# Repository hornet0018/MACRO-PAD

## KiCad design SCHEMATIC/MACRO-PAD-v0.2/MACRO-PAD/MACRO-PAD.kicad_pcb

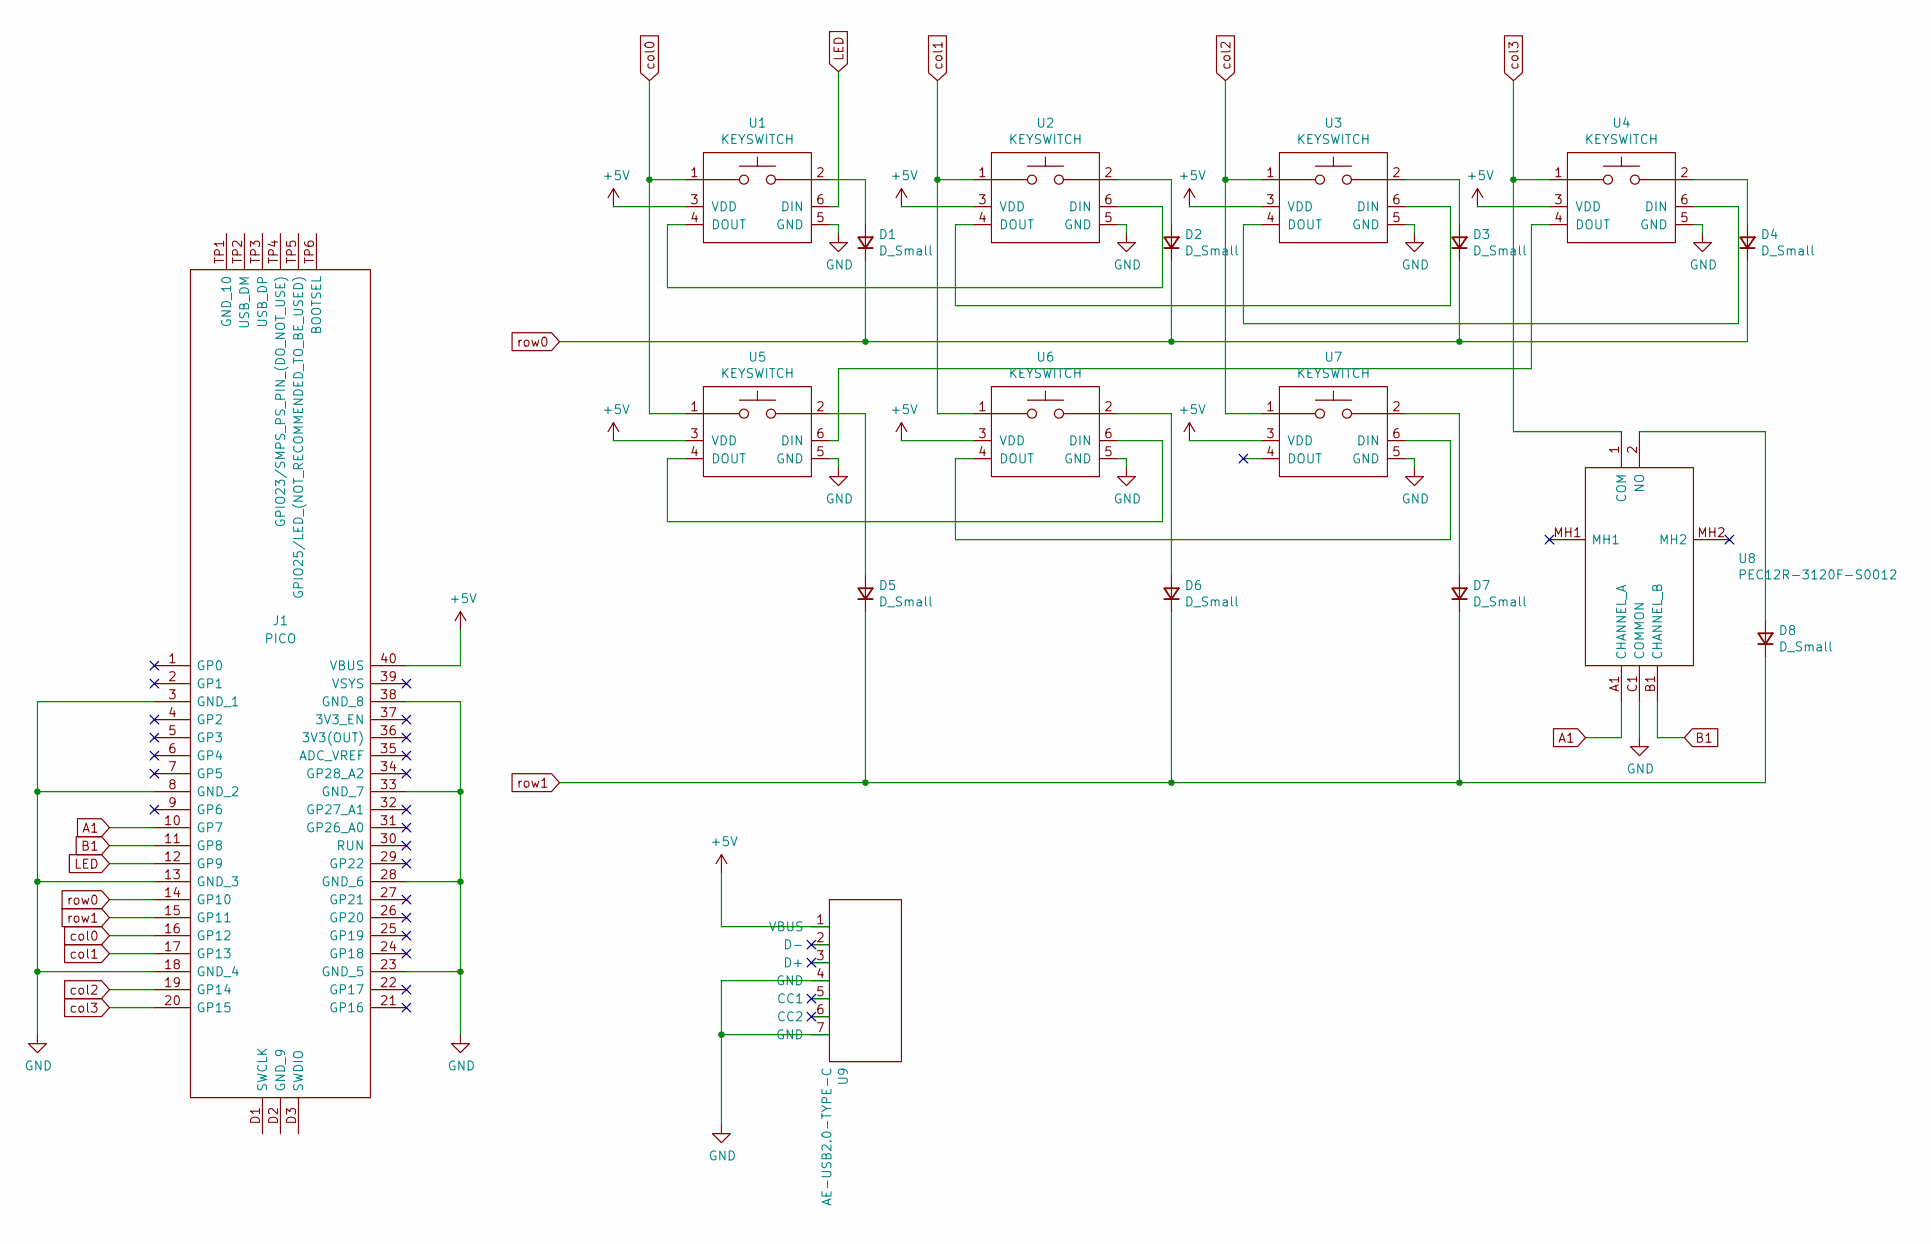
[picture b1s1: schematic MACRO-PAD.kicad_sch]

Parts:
D1, D2, D3, D4, D5, D6, D7, D8: D_Small; D_SOD-123
J1: PICO; RPi_Pico_SMD_TH; Manufacturer_Part_Number PICO
U1, U2, U3, U4, U5, U6, U7: KEYSWITCH; Kailh_socket_MX
U8: PEC12R-3120F-S0012; PEC12R3120FS0012; Manufacturer_Part_Number PEC12R-3120F-S0012; Mouser Part Number 652-PEC12R3120FS0012
U9: AE-USB2.0-TYPE-C

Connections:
+5V: J1.40 (VBUS), U1.3 (VDD), U2.3 (VDD), U3.3 (VDD), U4.3 (VDD), U5.3 (VDD), U6.3 (VDD), U7.3 (VDD), U9.1 (VBUS)
A1: J1.10 (GP7), U8.A1 (CHANNEL_A)
B1: J1.11 (GP8), U8.B1 (CHANNEL_B)
GND: J1.3 (GND_1), J1.8 (GND_2), J1.13 (GND_3), J1.18 (GND_4), J1.23 (GND_5), J1.28 (GND_6), J1.33 (GND_7), J1.38 (GND_8), U1.5 (GND), U2.5 (GND), U3.5 (GND), U4.5 (GND), U5.5 (GND), U6.5 (GND), U7.5 (GND), U8.C1 (COMMON), U9.4 (GND), U9.7 (GND)
LED: J1.12 (GP9), U1.6 (DIN)
unnamed: D1.2 (A), U1.2
unnamed: D2.2 (A), U2.2
unnamed: D3.2 (A), U3.2
unnamed: D4.2 (A), U4.2
unnamed: D5.2 (A), U5.2
unnamed: D6.2 (A), U6.2
unnamed: D7.2 (A), U7.2
unnamed: D8.2 (A), U8.2 (NO)
unnamed: U1.4 (DOUT), U2.6 (DIN)
unnamed: U2.4 (DOUT), U3.6 (DIN)
unnamed: U3.4 (DOUT), U4.6 (DIN)
unnamed: U4.4 (DOUT), U5.6 (DIN)
unnamed: U5.4 (DOUT), U6.6 (DIN)
unnamed: U6.4 (DOUT), U7.6 (DIN)
col0: J1.16 (GP12), U1.1, U5.1
col1: J1.17 (GP13), U2.1, U6.1
col2: J1.19 (GP14), U3.1, U7.1
col3: J1.20 (GP15), U4.1, U8.1 (COM)
row0: D1.1 (K), D2.1 (K), D3.1 (K), D4.1 (K), J1.14 (GP10)
row1: D5.1 (K), D6.1 (K), D7.1 (K), D8.1 (K), J1.15 (GP11)

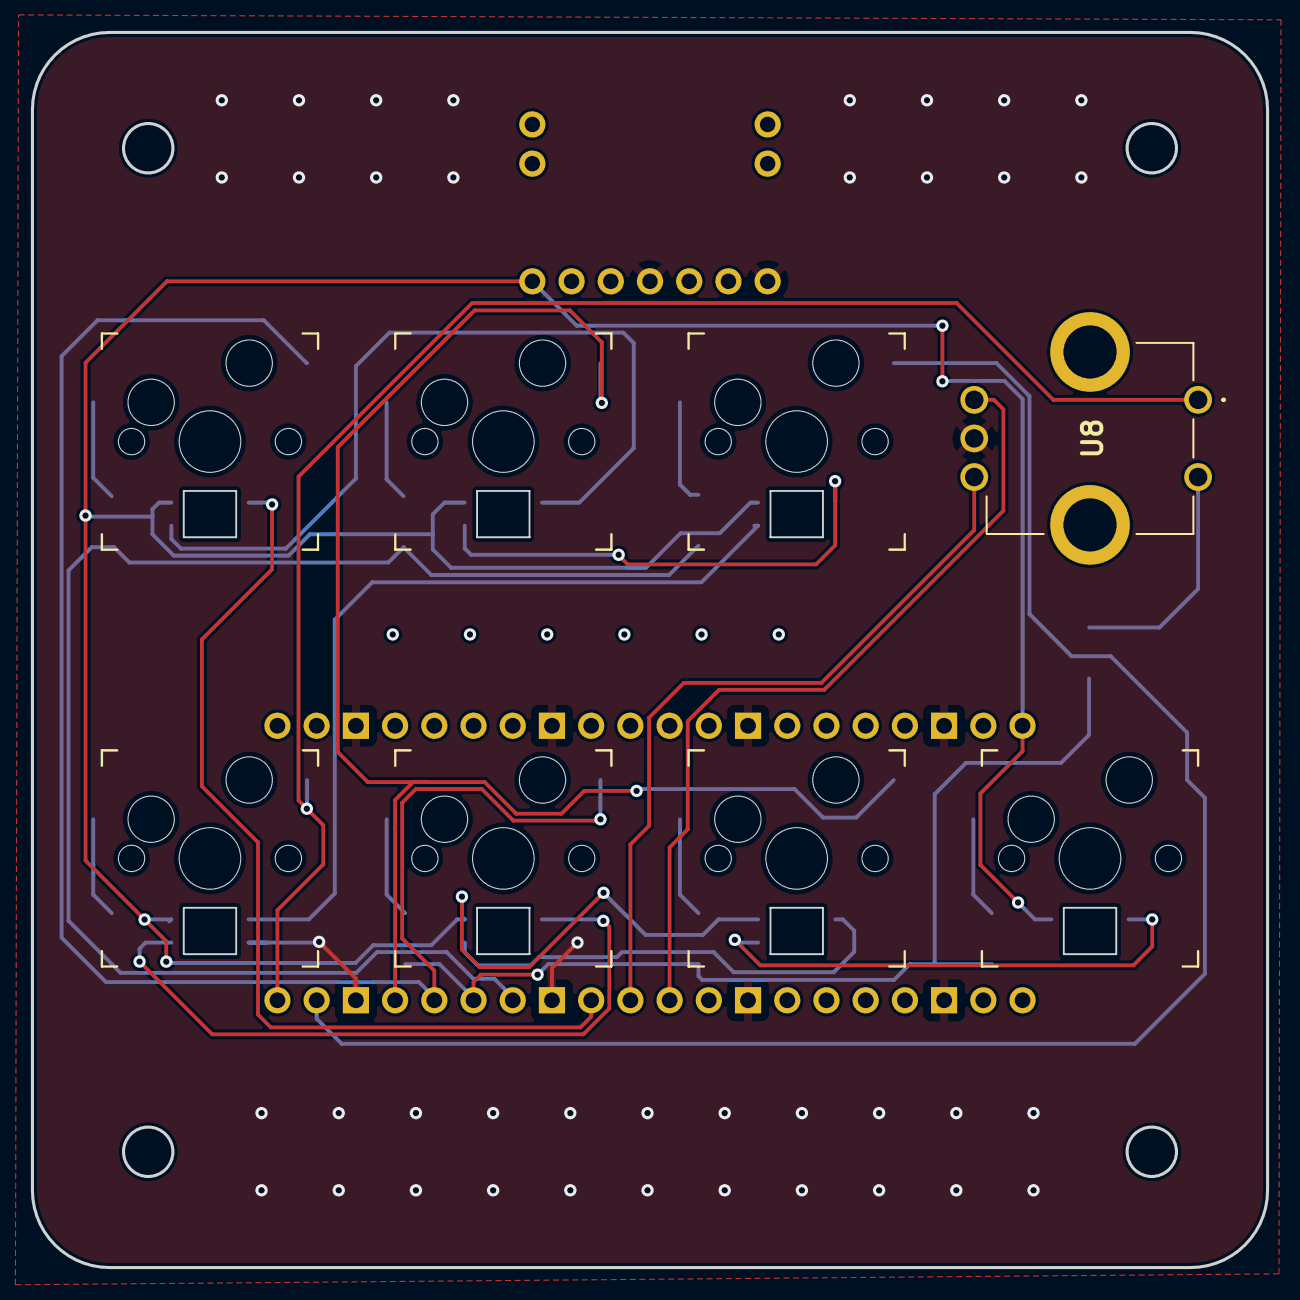
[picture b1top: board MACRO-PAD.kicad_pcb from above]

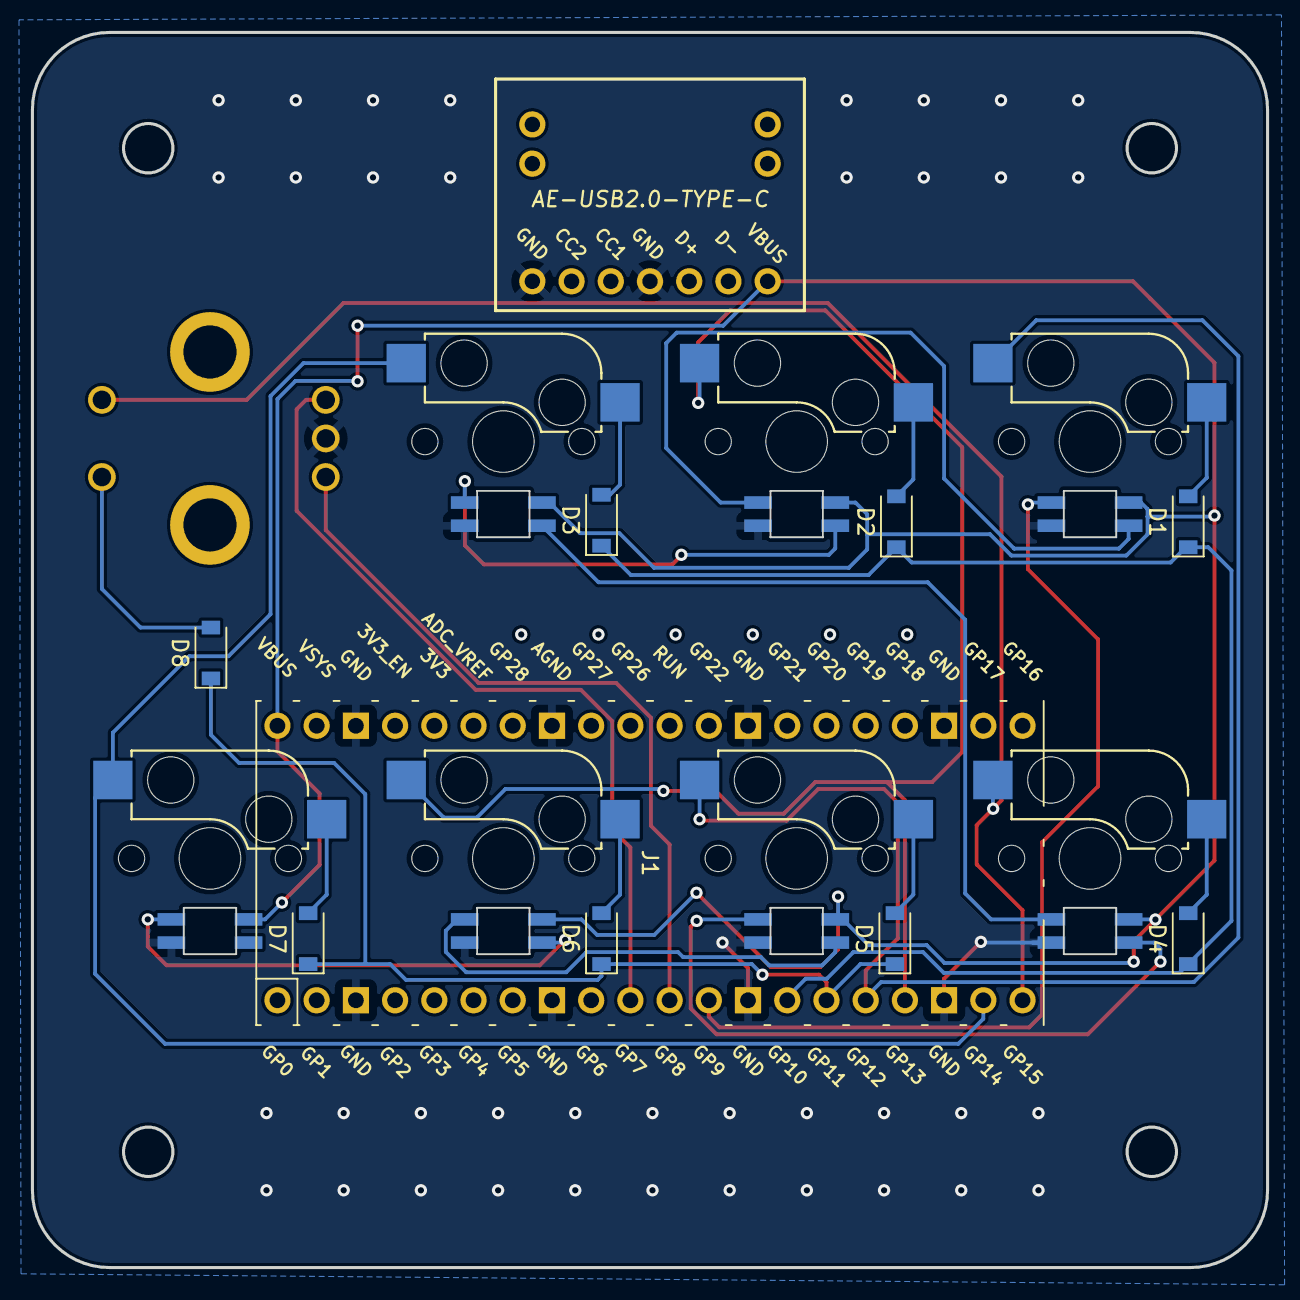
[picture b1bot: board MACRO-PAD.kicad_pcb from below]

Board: 2 copper layers, 80.0 x 80.0 mm, 18 parts (9 on the bottom side), 25 nets.

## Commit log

2022-01-02 update_v1.1
2022-01-03 create_v0.2
